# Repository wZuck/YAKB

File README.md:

# YAKB — Yet Another KeyBoard

[简体中文](README.zh-CN.md) · [B1.1 soldering workbench](hardware/soldering/b1/index.html) · [Assembly notes](docs/modular/README.md) · [File/revision map](docs/file-map.md)

The current assembly is the **B1.1 engineering prototype**: NiZ electrocapacitive mechanisms, a fixed 60-key HHKB layout, centered-stem 6u spacebar, nice!nano v2 / nRF52840 and ZMK, USB / BLE and a protected 1S battery.

The controller sits on a rear-left carrier, with USB-C directly accessible from the left side. Mainboard U1 takes only a passive interposer: **do not install a second controller there**. PCB, plate, case, fabrication files and geometry-based renders are supplied. Physical assembly, noise, RF, temperature and runtime remain untested. Qualify NiZ/stabilizer coupons, the short FPC and the rear-pod coupon before a complete build.

| Item | Current B1.1 definition |
| --- | --- |
| Layout | 60 keys, HHKB Control position, split right Shift + Fn; left blocker 1.5u, right 2.5u; centered 6u space with 95.25 mm stabilizer spacing |
| Mechanism / plate | NiZ housing, MX-cross slider, silencing ring, separate dome and sensing conical spring; 1.6 mm plate with initial 14.0 mm R0.5 cutouts; qualify in final material |
| Sensing mainboard | Shared A0 four-layer board, 285 × 94.6 × 1.6 mm; no MCU at U1 |
| Daughterboards / FPC | 82 × 24 × 1 mm carrier, 40 × 19 × 1 mm interposer; 24-conductor custom shaped FPC and Molex 200528-0240 connectors |
| Hand assembly | Mainly SOIC, 0805 and through holes; the 1 mm-pitch FPC connectors need flux and magnification; no bare MCU, crystal or RF network assembly |
| Power | Protected 1S, approximately 100 mA default charging, BOOST open; multiple pouches require a factory 1S2P / 1S3P pack with one protection board |
| USB / BLE | Direct to the carrier's nice!nano; Fn+5 selects USB, Fn+6 selects BLE; one reporting endpoint at a time |
| Case | Dedicated B1 base and pod lid with shared A0 HHKB bezel and plate; maximum plan envelope 299 × 136.6 mm, with 28 mm extra depth only at the rear-left pod; no visible top screws |
| Case compatibility | Mainboard mounts reference GH60 / Lot60; the B1 pod is not a universal drop-in fit for commercial GH60 / Poker cases |

B1.1 has **46 populated board/harness positions + one FPC**, plus one mainboard-U1 DNP record and 60 unsoldered sensing cells. No per-key diodes, hot-swap sockets, RGB, display or separate USB controller are used.

File entry points:

- [Complete electronics BOM](hardware/modular/BOM-B1-complete.csv), [module/case delta BOM](hardware/modular/BOM-B1.csv), [FPC pin map](hardware/modular/FPC-pinout.csv). The electronics BOM excludes batteries, mechanisms and case hardware; use the assembly notes and delta BOM for those.
- [Mainboard PCB](hardware/YAKB.kicad_pcb), [mainboard schematic](hardware/YAKB.kicad_sch), [controller PCB](hardware/modular/YAKB-controller-B1.kicad_pcb), [interposer PCB](hardware/modular/YAKB-interposer-B1.kicad_pcb), [custom FPC](hardware/modular/YAKB-shaped-FPC-B1.kicad_pcb). The shared mainboard source retains the A0 controller symbol; the consolidated BOM controls B1 population.
- [B1 assembly STEP](mechanical/modular/assembly_B1.step), [single-bay base STL](mechanical/modular/case_base_B1.stl), [three-bay base STL](mechanical/modular/case_base_B1_three_bay.stl), [pod lid](mechanical/modular/pod_lid_B1.stl), [shared bezel](mechanical/case_bezel.stl).
- [Own-case plate DXF](mechanical/plate_case.dxf), [NiZ coupon](mechanical/niz_fit_coupon.stl), [short-FPC ZIP](fabrication/modular/YAKB-FPC-coupon-B1.zip), [rear-pod print coupon](mechanical/modular/rear_pod_fit_coupon.stl). DXF units are mm; do not cut `REFERENCE`.
- [Interface corrections and qualification](docs/modular/interface-review.md), [firmware/flashing](firmware/README.md), [reproduction](docs/reproduce.md), [sources/licenses](docs/sources.md).

Scripts check native electrical reports, selected solid clearances, fabrication ZIPs and render hashes. See [reports](reports/) and the [consistency audit](docs/consistency-review.md) for coverage and pending physical tests. File checks do not certify hardware operation.

A0 is the baseline for the shared mainboard, bezel and plate. Its [historical workbench](hardware/soldering/index.html), [case record](docs/case-design.md), [base electrical analysis](docs/electrical-analysis.md) and [battery study](docs/battery-options.md) are explicitly scoped. The A0 base and incomplete USB extension arrangement are not used by the current B1 assembly.

Original YAKB files use MIT; reused Tako / KiCad library material retains its own licenses. See the source record for attribution boundaries.

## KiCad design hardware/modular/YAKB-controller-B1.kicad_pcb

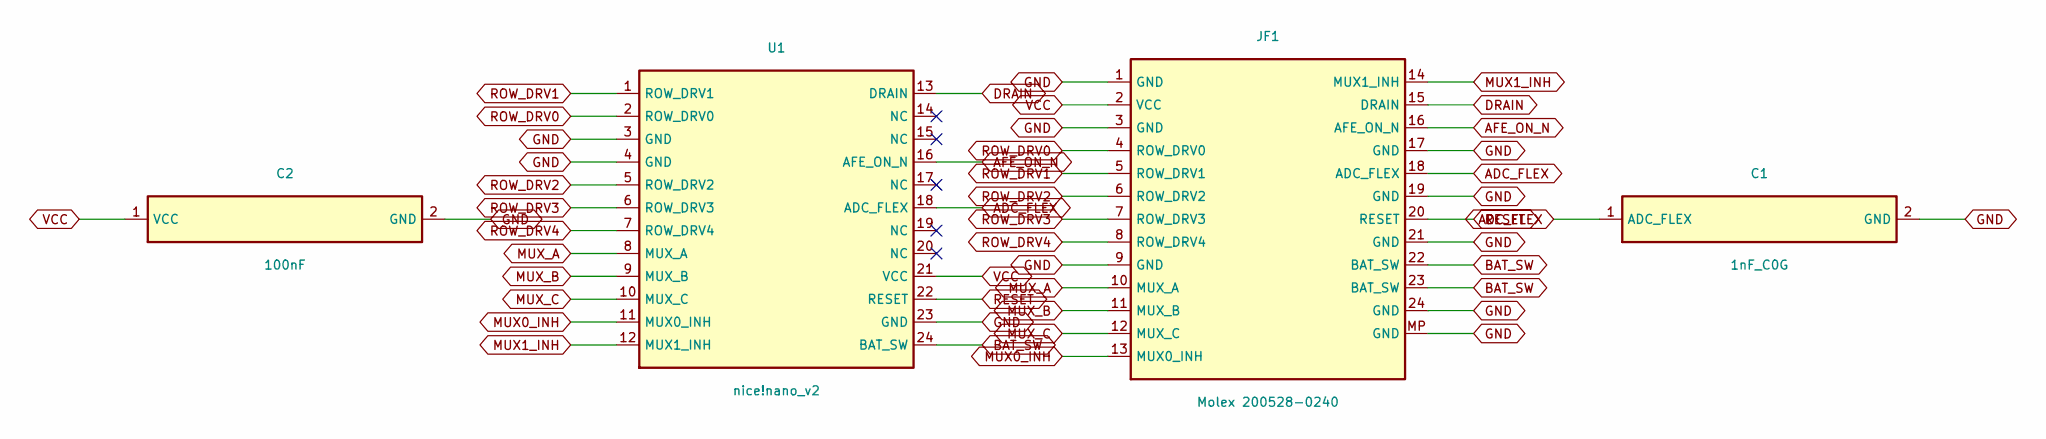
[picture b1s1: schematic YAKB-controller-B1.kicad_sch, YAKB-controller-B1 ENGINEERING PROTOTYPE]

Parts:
C1: 1nF_C0G; C_0805_2012Metric_Pad1.18x1.45mm_HandSolder
C2: 100nF; C_0805_2012Metric_Pad1.18x1.45mm_HandSolder
JF1: Molex 200528-0240; Molex_200528-0240_1x24-1MP_P1.00mm_Horizontal
U1: nice!nano_v2; nice_nano

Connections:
ADC_FLEX: C1.1 (ADC_FLEX), JF1.18 (ADC_FLEX), U1.18 (ADC_FLEX)
AFE_ON_N: JF1.16 (AFE_ON_N), U1.16 (AFE_ON_N)
BAT_SW: JF1.22 (BAT_SW), JF1.23 (BAT_SW), U1.24 (BAT_SW)
DRAIN: JF1.15 (DRAIN), U1.13 (DRAIN)
GND: C1.2 (GND), C2.2 (GND), JF1.1 (GND), JF1.3 (GND), JF1.9 (GND), JF1.17 (GND), JF1.19 (GND), JF1.21 (GND), JF1.24 (GND), JF1.MP (GND), U1.3 (GND), U1.4 (GND), U1.23 (GND)
MUX0_INH: JF1.13 (MUX0_INH), U1.11 (MUX0_INH)
MUX1_INH: JF1.14 (MUX1_INH), U1.12 (MUX1_INH)
MUX_A: JF1.10 (MUX_A), U1.8 (MUX_A)
MUX_B: JF1.11 (MUX_B), U1.9 (MUX_B)
MUX_C: JF1.12 (MUX_C), U1.10 (MUX_C)
RESET: JF1.20 (RESET), U1.22 (RESET)
ROW_DRV0: JF1.4 (ROW_DRV0), U1.2 (ROW_DRV0)
ROW_DRV1: JF1.5 (ROW_DRV1), U1.1 (ROW_DRV1)
ROW_DRV2: JF1.6 (ROW_DRV2), U1.5 (ROW_DRV2)
ROW_DRV3: JF1.7 (ROW_DRV3), U1.6 (ROW_DRV3)
ROW_DRV4: JF1.8 (ROW_DRV4), U1.7 (ROW_DRV4)
VCC: C2.1 (VCC), JF1.2 (VCC), U1.21 (VCC)

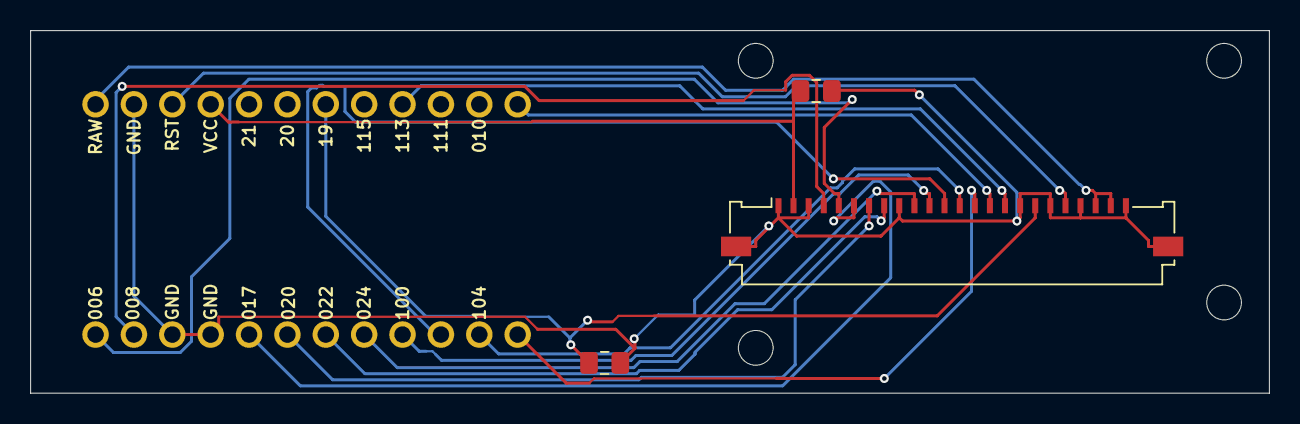
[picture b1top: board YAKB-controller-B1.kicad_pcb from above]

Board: 2 copper layers, 82.0 x 24.0 mm, 8 parts (0 on the bottom side), 17 nets.

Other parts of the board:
H1, H2, H3, H4: (no value)

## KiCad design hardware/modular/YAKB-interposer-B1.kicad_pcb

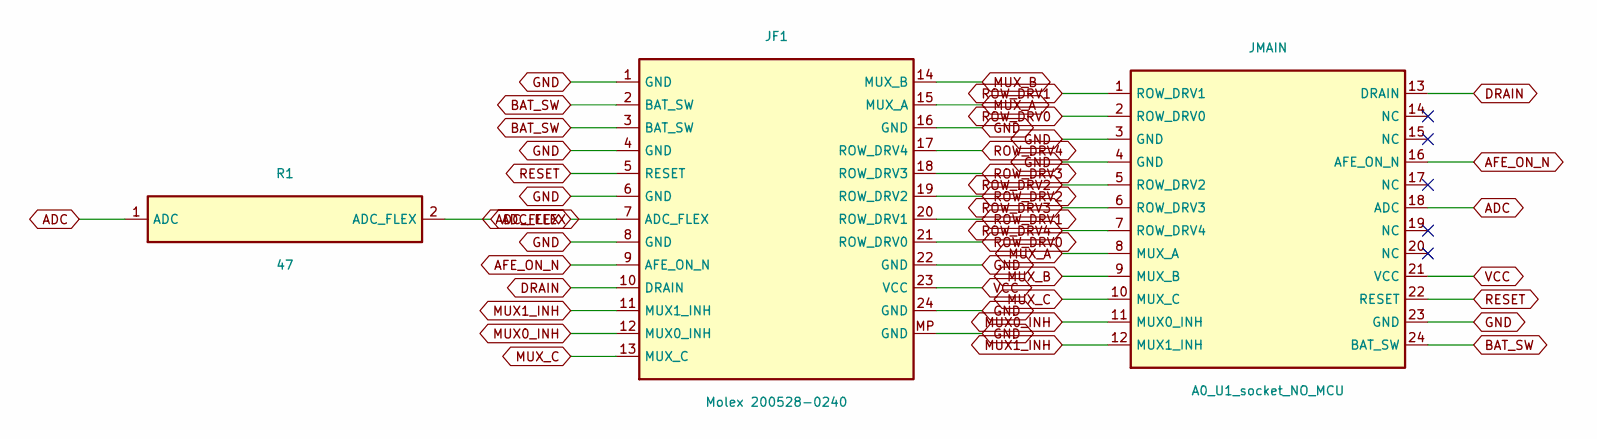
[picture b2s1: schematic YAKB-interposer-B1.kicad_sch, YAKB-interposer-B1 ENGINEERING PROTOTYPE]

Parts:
JF1: Molex 200528-0240; Molex_200528-0240_1x24-1MP_P1.00mm_Horizontal
JMAIN: A0_U1_socket_NO_MCU; A0_U1_socket_adapter
R1: 47; R_0805_2012Metric_Pad1.20x1.40mm_HandSolder

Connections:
ADC: JMAIN.18 (ADC), R1.1 (ADC)
ADC_FLEX: JF1.7 (ADC_FLEX), R1.2 (ADC_FLEX)
AFE_ON_N: JF1.9 (AFE_ON_N), JMAIN.16 (AFE_ON_N)
BAT_SW: JF1.2 (BAT_SW), JF1.3 (BAT_SW), JMAIN.24 (BAT_SW)
DRAIN: JF1.10 (DRAIN), JMAIN.13 (DRAIN)
GND: JF1.1 (GND), JF1.4 (GND), JF1.6 (GND), JF1.8 (GND), JF1.16 (GND), JF1.22 (GND), JF1.24 (GND), JF1.MP (GND), JMAIN.3 (GND), JMAIN.4 (GND), JMAIN.23 (GND)
MUX0_INH: JF1.12 (MUX0_INH), JMAIN.11 (MUX0_INH)
MUX1_INH: JF1.11 (MUX1_INH), JMAIN.12 (MUX1_INH)
MUX_A: JF1.15 (MUX_A), JMAIN.8 (MUX_A)
MUX_B: JF1.14 (MUX_B), JMAIN.9 (MUX_B)
MUX_C: JF1.13 (MUX_C), JMAIN.10 (MUX_C)
RESET: JF1.5 (RESET), JMAIN.22 (RESET)
ROW_DRV0: JF1.21 (ROW_DRV0), JMAIN.2 (ROW_DRV0)
ROW_DRV1: JF1.20 (ROW_DRV1), JMAIN.1 (ROW_DRV1)
ROW_DRV2: JF1.19 (ROW_DRV2), JMAIN.5 (ROW_DRV2)
ROW_DRV3: JF1.18 (ROW_DRV3), JMAIN.6 (ROW_DRV3)
ROW_DRV4: JF1.17 (ROW_DRV4), JMAIN.7 (ROW_DRV4)
VCC: JF1.23 (VCC), JMAIN.21 (VCC)

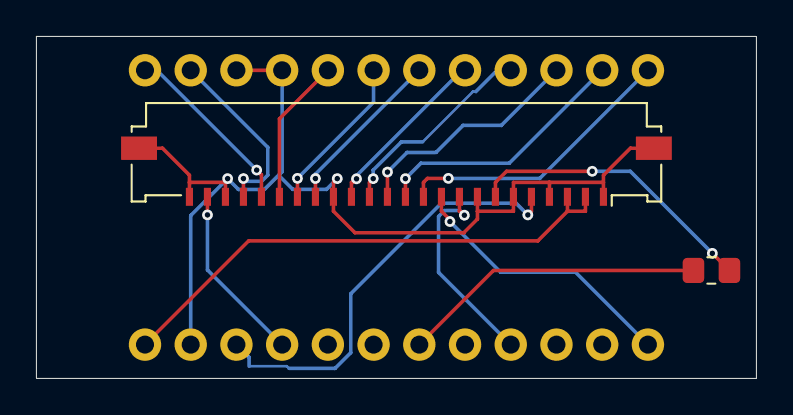
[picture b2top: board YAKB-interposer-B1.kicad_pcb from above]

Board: 2 copper layers, 40.0 x 19.0 mm, 3 parts (0 on the bottom side), 18 nets.

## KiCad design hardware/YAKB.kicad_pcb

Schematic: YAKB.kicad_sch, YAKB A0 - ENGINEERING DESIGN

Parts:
C1, C2, C3: 100n; C_0805_2012Metric_Pad1.18x1.45mm_HandSolder
C4: 220p_C0G; C_0805_2012Metric_Pad1.18x1.45mm_HandSolder
C5: 1u; C_0805_2012Metric_Pad1.18x1.45mm_HandSolder
EC1: Esc; ecs_pad_1U_no_ring
EC2: 1; ecs_pad_1U_no_ring
EC3: 2; ecs_pad_1U_no_ring
EC4: 3; ecs_pad_1U_no_ring
EC5: 4; ecs_pad_1U_no_ring
EC6: 5; ecs_pad_1U_no_ring
EC7: 6; ecs_pad_1U_no_ring
EC8: 7; ecs_pad_1U_no_ring
EC9: 8; ecs_pad_1U_no_ring
EC10: 9; ecs_pad_1U_no_ring
EC11: 0; ecs_pad_1U_no_ring
EC12: -; ecs_pad_1U_no_ring
EC13: =; ecs_pad_1U_no_ring
EC14: \; ecs_pad_1U_no_ring
EC15: `; ecs_pad_1U_no_ring
EC16: Tab; ecs_pad_1U_no_ring
EC17: Q; ecs_pad_1U_no_ring
EC18: W; ecs_pad_1U_no_ring
EC19: E; ecs_pad_1U_no_ring
EC20: R; ecs_pad_1U_no_ring
EC21: T; ecs_pad_1U_no_ring
EC22: Y; ecs_pad_1U_no_ring
EC23: U; ecs_pad_1U_no_ring
EC24: I; ecs_pad_1U_no_ring
EC25: O; ecs_pad_1U_no_ring
EC26: P; ecs_pad_1U_no_ring
EC27: [; ecs_pad_1U_no_ring
EC28: ]; ecs_pad_1U_no_ring
EC29: Backspace; ecs_pad_1U_no_ring
EC30: Control; ecs_pad_1U_no_ring
EC31: A; ecs_pad_1U_no_ring
EC32: S; ecs_pad_1U_no_ring
EC33: D; ecs_pad_1U_no_ring
EC34: F; ecs_pad_1U_no_ring
EC35: G; ecs_pad_1U_no_ring
EC36: H; ecs_pad_1U_no_ring
EC37: J; ecs_pad_1U_no_ring
EC38: K; ecs_pad_1U_no_ring
EC39: L; ecs_pad_1U_no_ring
EC40: ;; ecs_pad_1U_no_ring
EC41: '; ecs_pad_1U_no_ring
EC42: Enter; ecs_pad_1U_no_ring
EC43: Shift; ecs_pad_1U_no_ring
EC44: Z; ecs_pad_1U_no_ring
EC45: X; ecs_pad_1U_no_ring
EC46: C; ecs_pad_1U_no_ring
EC47: V; ecs_pad_1U_no_ring
EC48: B; ecs_pad_1U_no_ring
EC49: N; ecs_pad_1U_no_ring
EC50: M; ecs_pad_1U_no_ring
EC51: ,; ecs_pad_1U_no_ring
EC52: .; ecs_pad_1U_no_ring
EC53: /; ecs_pad_1U_no_ring
EC54: RShift; ecs_pad_1U_no_ring
EC55: Fn; ecs_pad_1U_no_ring
EC56: LGUI; ecs_pad_1U_no_ring
EC57: LAlt; ecs_pad_1U_no_ring
EC58: Space; ecs_pad_1U_no_ring
EC59: RAlt; ecs_pad_1U_no_ring
EC60: RGUI; ecs_pad_1U_no_ring
J1: JST_S2B-PH-K; Battery_PH2
Q1: AO3401A; SOT-23
R1, R2, R3, R4, R5: 100; R_0805_2012Metric_Pad1.20x1.40mm_HandSolder
R10, R11, R12, R13, R14, R15, R16, R17, R18, R19, R20, R21, R22, R23, R24, R30, R33, R34, R35: 100k; R_0805_2012Metric_Pad1.20x1.40mm_HandSolder
R31, R32, R36: 1k; R_0805_2012Metric_Pad1.20x1.40mm_HandSolder
SW1: Battery_switch_pigtail; SPST_PIGTAIL_2.54
SW2: Reset_NO; RESET_2.54_TH
U1: nice!nano_v2; nice_nano
U2, U3: CD74HC4051M96; SOIC-16_3.9x9.9mm_P1.27mm
U4: OPA350UA; SOIC-8_3.9x4.9mm_P1.27mm

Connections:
ADC: R30.1 (ADC), U1.18 (D19/P0.02/AIN0), U4.6 (OUT)
AFE_3V3: C3.1 (AFE_3V3), Q1.3 (D), U4.7 (V+)
AFE_GATE: Q1.1 (G), R35.1 (AFE_GATE), R36.2 (AFE_GATE)
AFE_ON_N: R36.1 (AFE_ON_N), U1.16 (D15/P1.13)
BAT_RAW: J1.1 (BAT_RAW), SW1.1 (BAT_RAW)
BAT_SW: SW1.2 (BAT_SW), U1.24 (BATTERY+)
COL0: EC1.2 (SENSE), EC16.2 (SENSE), EC30.2 (SENSE), R10.1 (COL0), U2.13 (X0)
COL1: EC2.2 (SENSE), EC43.2 (SENSE), R11.1 (COL1), U2.14 (X1)
COL2: EC3.2 (SENSE), EC17.2 (SENSE), EC31.2 (SENSE), EC44.2 (SENSE), EC56.2 (SENSE), R12.1 (COL2), U2.15 (X2)
COL3: EC4.2 (SENSE), EC18.2 (SENSE), EC32.2 (SENSE), EC45.2 (SENSE), EC57.2 (SENSE), R13.1 (COL3), U2.12 (X3)
COL4: EC5.2 (SENSE), EC19.2 (SENSE), EC33.2 (SENSE), EC46.2 (SENSE), R14.1 (COL4), U2.1 (X4)
COL5: EC6.2 (SENSE), EC20.2 (SENSE), EC34.2 (SENSE), EC47.2 (SENSE), R15.1 (COL5), U2.5 (X5)
COL6: EC7.2 (SENSE), EC21.2 (SENSE), EC35.2 (SENSE), EC48.2 (SENSE), R16.1 (COL6), U2.2 (X6)
COL7: EC8.2 (SENSE), EC22.2 (SENSE), EC36.2 (SENSE), EC49.2 (SENSE), EC58.2 (SENSE), R17.1 (COL7), U2.4 (X7)
COL8: EC9.2 (SENSE), EC23.2 (SENSE), EC37.2 (SENSE), EC50.2 (SENSE), R18.1 (COL8), U3.13 (X0)
COL9: EC10.2 (SENSE), EC24.2 (SENSE), EC38.2 (SENSE), EC51.2 (SENSE), R19.1 (COL9), U3.14 (X1)
COL10: EC11.2 (SENSE), EC25.2 (SENSE), EC39.2 (SENSE), EC52.2 (SENSE), EC59.2 (SENSE), R20.1 (COL10), U3.15 (X2)
COL11: EC12.2 (SENSE), EC26.2 (SENSE), EC40.2 (SENSE), EC53.2 (SENSE), R21.1 (COL11), U3.12 (X3)
COL12: EC13.2 (SENSE), EC27.2 (SENSE), EC41.2 (SENSE), EC60.2 (SENSE), R22.1 (COL12), U3.1 (X4)
COL13: EC14.2 (SENSE), EC28.2 (SENSE), EC42.2 (SENSE), EC54.2 (SENSE), R23.1 (COL13), U3.5 (X5)
COL14: EC15.2 (SENSE), EC29.2 (SENSE), EC55.2 (SENSE), R24.1 (COL14), U3.2 (X6)
DRAIN: R32.1 (DRAIN), U1.13 (D10/P0.09)
FB: R30.2 (FB), R31.1 (FB), U4.2 (IN-)
GND: C1.2 (GND), C2.2 (GND), C3.2 (GND), C4.2 (GND), C5.2 (GND), EC1.3 (GUARD), EC2.3 (GUARD), EC3.3 (GUARD), EC4.3 (GUARD), EC5.3 (GUARD), EC6.3 (GUARD), EC7.3 (GUARD), EC8.3 (GUARD), EC9.3 (GUARD), EC10.3 (GUARD), EC11.3 (GUARD), EC12.3 (GUARD), EC13.3 (GUARD), EC14.3 (GUARD), EC15.3 (GUARD), EC16.3 (GUARD), EC17.3 (GUARD), EC18.3 (GUARD), EC19.3 (GUARD), EC20.3 (GUARD), EC21.3 (GUARD), EC22.3 (GUARD), EC23.3 (GUARD), EC24.3 (GUARD), EC25.3 (GUARD), EC26.3 (GUARD), EC27.3 (GUARD), EC28.3 (GUARD), EC29.3 (GUARD), EC30.3 (GUARD), EC31.3 (GUARD), EC32.3 (GUARD), EC33.3 (GUARD), EC34.3 (GUARD), EC35.3 (GUARD), EC36.3 (GUARD), EC37.3 (GUARD), EC38.3 (GUARD), EC39.3 (GUARD), EC40.3 (GUARD), EC41.3 (GUARD), EC42.3 (GUARD), EC43.3 (GUARD), EC44.3 (GUARD), EC45.3 (GUARD), EC46.3 (GUARD), EC47.3 (GUARD), EC48.3 (GUARD), EC49.3 (GUARD), EC50.3 (GUARD), EC51.3 (GUARD), EC52.3 (GUARD), EC53.3 (GUARD), EC54.3 (GUARD), EC55.3 (GUARD), EC56.3 (GUARD), EC57.3 (GUARD), EC58.3 (GUARD), EC59.3 (GUARD), EC60.3 (GUARD), J1.2 (GND), R10.2 (GND), R11.2 (GND), R12.2 (GND), R13.2 (GND), R14.2 (GND), R15.2 (GND), R16.2 (GND), R17.2 (GND), R18.2 (GND), R19.2 (GND), R20.2 (GND), R21.2 (GND), R22.2 (GND), R23.2 (GND), R24.2 (GND), R31.2 (GND), SW2.2 (GND), U1.3 (GND), U1.4 (GND), U1.23 (GND), U2.7 (VEE), U2.8 (GND), U3.4 (X7), U3.7 (VEE), U3.8 (GND), U4.4 (V-)
MUX0_INH: R33.1 (MUX0_INH), U1.11 (D8/P1.04), U2.6 (INH)
MUX1_INH: R34.1 (MUX1_INH), U1.12 (D9/P1.06), U3.6 (INH)
MUX_A: U1.8 (D5/P0.24), U2.11 (A), U3.11 (A)
MUX_B: U1.9 (D6/P1.00), U2.10 (B), U3.10 (B)
MUX_C: U1.10 (D7/P0.11), U2.9 (C), U3.9 (C)
RESET: SW2.1 (RESET), U1.22 (RESET)
ROW0: EC1.1 (DRIVE), EC2.1 (DRIVE), EC3.1 (DRIVE), EC4.1 (DRIVE), EC5.1 (DRIVE), EC6.1 (DRIVE), EC7.1 (DRIVE), EC8.1 (DRIVE), EC9.1 (DRIVE), EC10.1 (DRIVE), EC11.1 (DRIVE), EC12.1 (DRIVE), EC13.1 (DRIVE), EC14.1 (DRIVE), EC15.1 (DRIVE), R1.2 (ROW0)
ROW1: EC16.1 (DRIVE), EC17.1 (DRIVE), EC18.1 (DRIVE), EC19.1 (DRIVE), EC20.1 (DRIVE), EC21.1 (DRIVE), EC22.1 (DRIVE), EC23.1 (DRIVE), EC24.1 (DRIVE), EC25.1 (DRIVE), EC26.1 (DRIVE), EC27.1 (DRIVE), EC28.1 (DRIVE), EC29.1 (DRIVE), R2.2 (ROW1)
ROW2: EC30.1 (DRIVE), EC31.1 (DRIVE), EC32.1 (DRIVE), EC33.1 (DRIVE), EC34.1 (DRIVE), EC35.1 (DRIVE), EC36.1 (DRIVE), EC37.1 (DRIVE), EC38.1 (DRIVE), EC39.1 (DRIVE), EC40.1 (DRIVE), EC41.1 (DRIVE), EC42.1 (DRIVE), R3.2 (ROW2)
ROW3: EC43.1 (DRIVE), EC44.1 (DRIVE), EC45.1 (DRIVE), EC46.1 (DRIVE), EC47.1 (DRIVE), EC48.1 (DRIVE), EC49.1 (DRIVE), EC50.1 (DRIVE), EC51.1 (DRIVE), EC52.1 (DRIVE), EC53.1 (DRIVE), EC54.1 (DRIVE), EC55.1 (DRIVE), R4.2 (ROW3)
ROW4: EC56.1 (DRIVE), EC57.1 (DRIVE), EC58.1 (DRIVE), EC59.1 (DRIVE), EC60.1 (DRIVE), R5.2 (ROW4)
ROW_DRV0: R1.1 (ROW_DRV0), U1.2 (D0/P0.08)
ROW_DRV1: R2.1 (ROW_DRV1), U1.1 (D1/P0.06)
ROW_DRV2: R3.1 (ROW_DRV2), U1.5 (D2/P0.17)
ROW_DRV3: R4.1 (ROW_DRV3), U1.6 (D3/P0.20)
ROW_DRV4: R5.1 (ROW_DRV4), U1.7 (D4/P0.22)
SENSE: C4.1 (SENSE), R32.2 (SENSE), U2.3 (COM), U3.3 (COM), U4.3 (IN+)
VCC: C1.1 (VCC), C2.1 (VCC), C5.1 (VCC), Q1.2 (S), R33.2 (VCC), R34.2 (VCC), R35.2 (VCC), U1.21 (VCC_3.3V), U2.16 (VCC), U3.16 (VCC)

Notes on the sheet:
YAKB A0 | NiZ EC + HHKB 6u + nice!nano v2 | ENGINEERING PROTOTYPE
Physical pin numbers and named nets are authoritative. USB is an external passive data extension to U1.
U2/U3: only one INH low at a time. U4 gain 101. DRAIN goes through R32 to SENSE. Q1 gates U4 only.
SW1/SW2 are 2.54mm solder-hole harnesses. No external 5V connection to U1 BATTERY+.
EC electrodes: logical row = physical row; column = floor(x_u + width_u/2), including empty column bins.

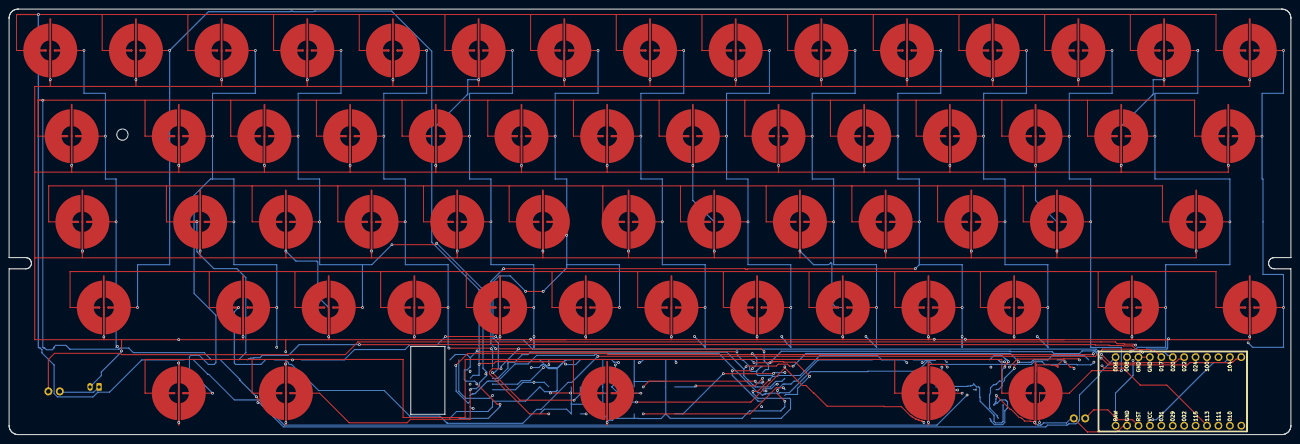
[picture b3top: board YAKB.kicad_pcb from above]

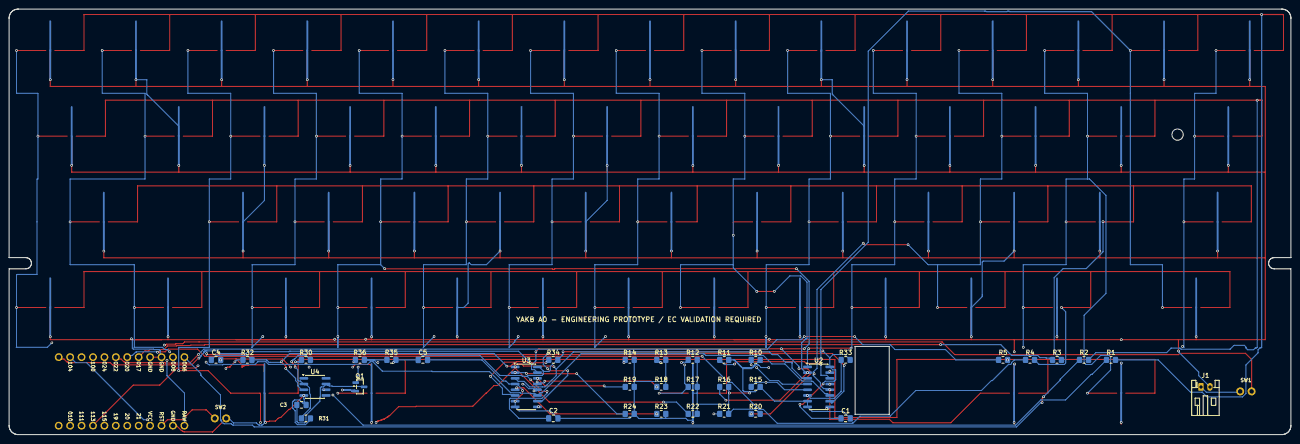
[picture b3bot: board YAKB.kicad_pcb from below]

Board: 4 copper layers, 285.0 x 94.6 mm, 103 parts (40 on the bottom side), 42 nets.

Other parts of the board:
H_center: (no value)
H_lower_center: (no value)
H_upper_left: (no value)

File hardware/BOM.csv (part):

Reference,Value,Footprint,Side,X_mm,Y_mm,Status
U1,nice!nano_v2,YAKB:nice_nano,B,260.0,85.0,selection; verify procurement
U2,SN74HC4051D,Package_SO:SOIC-16_3.9x9.9mm_P1.27mm,B,105,84,selection; verify procurement
U3,SN74HC4051D,Package_SO:SOIC-16_3.9x9.9mm_P1.27mm,B,170,84,selection; verify procurement
U4,OPA350UA,Package_SO:SOIC-8_3.9x4.9mm_P1.27mm,B,217,84,selection; verify procurement
Q1,AO3401A,Package_TO_SOT_SMD:SOT-23,B,207,84,selection; verify procurement
R1,100,Resistor_SMD:R_0805_2012Metric_Pad1.20x1.40mm_HandSolder,B,40,78,selection; verify procurement
R2,100,Resistor_SMD:R_0805_2012Metric_Pad1.20x1.40mm_HandSolder,B,46,78,selection; verify procurement
R3,100,Resistor_SMD:R_0805_2012Metric_Pad1.20x1.40mm_HandSolder,B,52,78,selection; verify procurement
R4,100,Resistor_SMD:R_0805_2012Metric_Pad1.20x1.40mm_HandSolder,B,58,78,selection; verify procurement
R5,100,Resistor_SMD:R_0805_2012Metric_Pad1.20x1.40mm_HandSolder,B,64,78,selection; verify procurement
R10,100k,Resistor_SMD:R_0805_2012Metric_Pad1.20x1.40mm_HandSolder,B,119,78,selection; verify procurement
R11,100k,Resistor_SMD:R_0805_2012Metric_Pad1.20x1.40mm_HandSolder,B,126,78,selection; verify procurement
R12,100k,Resistor_SMD:R_0805_2012Metric_Pad1.20x1.40mm_HandSolder,B,133,78,selection; verify procurement
R13,100k,Resistor_SMD:R_0805_2012Metric_Pad1.20x1.40mm_HandSolder,B,140,78,selection; verify procurement
R14,100k,Resistor_SMD:R_0805_2012Metric_Pad1.20x1.40mm_HandSolder,B,147,78,selection; verify procurement
R15,100k,Resistor_SMD:R_0805_2012Metric_Pad1.20x1.40mm_HandSolder,B,119,84,selection; verify procurement
R16,100k,Resistor_SMD:R_0805_2012Metric_Pad1.20x1.40mm_HandSolder,B,126,84,selection; verify procurement
R17,100k,Resistor_SMD:R_0805_2012Metric_Pad1.20x1.40mm_HandSolder,B,133,84,selection; verify procurement
R18,100k,Resistor_SMD:R_0805_2012Metric_Pad1.20x1.40mm_HandSolder,B,140,84,selection; verify procurement
R19,100k,Resistor_SMD:R_0805_2012Metric_Pad1.20x1.40mm_HandSolder,B,147,84,selection; verify procurement
R20,100k,Resistor_SMD:R_0805_2012Metric_Pad1.20x1.40mm_HandSolder,B,119,90,selection; verify procurement
R21,100k,Resistor_SMD:R_0805_2012Metric_Pad1.20x1.40mm_HandSolder,B,126,90,selection; verify procurement
R22,100k,Resistor_SMD:R_0805_2012Metric_Pad1.20x1.40mm_HandSolder,B,133,90,selection; verify procurement
R23,100k,Resistor_SMD:R_0805_2012Metric_Pad1.20x1.40mm_HandSolder,B,140,90,selection; verify procurement
R24,100k,Resistor_SMD:R_0805_2012Metric_Pad1.20x1.40mm_HandSolder,B,147,90,selection; verify procurement
R30,100k,Resistor_SMD:R_0805_2012Metric_Pad1.20x1.40mm_HandSolder,B,219,78,selection; verify procurement
R31,1k,Resistor_SMD:R_0805_2012Metric_Pad1.20x1.40mm_HandSolder,B,219,91,selection; verify procurement
R32,1k,Resistor_SMD:R_0805_2012Metric_Pad1.20x1.40mm_HandSolder,B,232,78,selection; verify procurement
R33,100k,Resistor_SMD:R_0805_2012Metric_Pad1.20x1.40mm_HandSolder,B,99,78,selection; verify procurement
R34,100k,Resistor_SMD:R_0805_2012Metric_Pad1.20x1.40mm_HandSolder,B,164,78,selection; verify procurement
R35,100k,Resistor_SMD:R_0805_2012Metric_Pad1.20x1.40mm_HandSolder,B,200,78,selection; verify procurement
R36,1k,Resistor_SMD:R_0805_2012Metric_Pad1.20x1.40mm_HandSolder,B,207,78,selection; verify procurement
C1,100n,Capacitor_SMD:C_0805_2012Metric_Pad1.18x1.45mm_HandSolder,B,99,91,selection; verify procurement
C2,100n,Capacitor_SMD:C_0805_2012Metric_Pad1.18x1.45mm_HandSolder,B,164,91,selection; verify procurement
C3,100n,Capacitor_SMD:C_0805_2012Metric_Pad1.18x1.45mm_HandSolder,B,220,88,selection; verify procurement
C4,220p_C0G,Capacitor_SMD:C_0805_2012Metric_Pad1.18x1.45mm_HandSolder,B,239,78,selection; verify procurement
C5,1u,Capacitor_SMD:C_0805_2012Metric_Pad1.18x1.45mm_HandSolder,B,193,78,selection; verify procurement
J1,JST_S2B-PH-K,YAKB:Battery_PH2,B,20,84,selection; verify procurement
SW1,Battery_switch_pigtail,YAKB:SPST_PIGTAIL_2.54,B,10,85,selection; verify procurement
SW2,Reset_NO,YAKB:RESET_2.54_TH,B,238,91,selection; verify procurement
EC1,Esc,YAKB:ecs_pad_1U_no_ring,F,9.15,9.2,EC electrode
EC2,1,YAKB:ecs_pad_1U_no_ring,F,28.200000000000003,9.2,EC electrode
EC3,2,YAKB:ecs_pad_1U_no_ring,F,47.25,9.2,EC electrode
EC4,3,YAKB:ecs_pad_1U_no_ring,F,66.30000000000001,9.2,EC electrode
EC5,4,YAKB:ecs_pad_1U_no_ring,F,85.35000000000001,9.2,EC electrode
EC6,5,YAKB:ecs_pad_1U_no_ring,F,104.4,9.2,EC electrode
EC7,6,YAKB:ecs_pad_1U_no_ring,F,123.45000000000002,9.2,EC electrode
EC8,7,YAKB:ecs_pad_1U_no_ring,F,142.5,9.2,EC electrode
EC9,8,YAKB:ecs_pad_1U_no_ring,F,161.55,9.2,EC electrode
EC10,9,YAKB:ecs_pad_1U_no_ring,F,180.60000000000002,9.2,EC electrode
EC11,0,YAKB:ecs_pad_1U_no_ring,F,199.65,9.2,EC electrode
EC12,-,YAKB:ecs_pad_1U_no_ring,F,218.70000000000002,9.2,EC electrode
EC13,=,YAKB:ecs_pad_1U_no_ring,F,237.75000000000003,9.2,EC electrode
EC14,\,YAKB:ecs_pad_1U_no_ring,F,256.8,9.2,EC electrode
EC15,`,YAKB:ecs_pad_1U_no_ring,F,275.84999999999997,9.2,EC electrode
EC16,Tab,YAKB:ecs_pad_1U_no_ring,F,13.912500000000001,28.25,EC electrode
EC17,Q,YAKB:ecs_pad_1U_no_ring,F,37.725,28.25,EC electrode
EC18,W,YAKB:ecs_pad_1U_no_ring,F,56.775,28.25,EC electrode
EC19,E,YAKB:ecs_pad_1U_no_ring,F,75.825,28.25,EC electrode
EC20,R,YAKB:ecs_pad_1U_no_ring,F,94.87500000000001,28.25,EC electrode
EC21,T,YAKB:ecs_pad_1U_no_ring,F,113.92500000000001,28.25,EC electrode
EC22,Y,YAKB:ecs_pad_1U_no_ring,F,132.975,28.25,EC electrode
EC23,U,YAKB:ecs_pad_1U_no_ring,F,152.025,28.25,EC electrode
EC24,I,YAKB:ecs_pad_1U_no_ring,F,171.07500000000002,28.25,EC electrode
EC25,O,YAKB:ecs_pad_1U_no_ring,F,190.125,28.25,EC electrode
EC26,P,YAKB:ecs_pad_1U_no_ring,F,209.175,28.25,EC electrode
EC27,[,YAKB:ecs_pad_1U_no_ring,F,228.22500000000002,28.25,EC electrode
EC28,],YAKB:ecs_pad_1U_no_ring,F,247.275,28.25,EC electrode
EC29,Backspace,YAKB:ecs_pad_1U_no_ring,F,271.0875,28.25,EC electrode
EC30,Control,YAKB:ecs_pad_1U_no_ring,F,16.293750000000003,47.3,EC electrode
EC31,A,YAKB:ecs_pad_1U_no_ring,F,42.4875,47.3,EC electrode
EC32,S,YAKB:ecs_pad_1U_no_ring,F,61.5375,47.3,EC electrode
EC33,D,YAKB:ecs_pad_1U_no_ring,F,80.5875,47.3,EC electrode
EC34,F,YAKB:ecs_pad_1U_no_ring,F,99.6375,47.3,EC electrode
EC35,G,YAKB:ecs_pad_1U_no_ring,F,118.68750000000001,47.3,EC electrode
EC36,H,YAKB:ecs_pad_1U_no_ring,F,137.7375,47.3,EC electrode
EC37,J,YAKB:ecs_pad_1U_no_ring,F,156.78750000000002,47.3,EC electrode
EC38,K,YAKB:ecs_pad_1U_no_ring,F,175.8375,47.3,EC electrode
EC39,L,YAKB:ecs_pad_1U_no_ring,F,194.88750000000002,47.3,EC electrode
EC40,;,YAKB:ecs_pad_1U_no_ring,F,213.9375,47.3,EC electrode
EC41,',YAKB:ecs_pad_1U_no_ring,F,232.9875,47.3,EC electrode
EC42,Enter,YAKB:ecs_pad_1U_no_ring,F,263.94375,47.3,EC electrode
EC43,Shift,YAKB:ecs_pad_1U_no_ring,F,21.05625,66.35000000000001,EC electrode
EC44,Z,YAKB:ecs_pad_1U_no_ring,F,52.0125,66.35000000000001,EC electrode
EC45,X,YAKB:ecs_pad_1U_no_ring,F,71.0625,66.35000000000001,EC electrode
EC46,C,YAKB:ecs_pad_1U_no_ring,F,90.11250000000001,66.35000000000001,EC electrode
EC47,V,YAKB:ecs_pad_1U_no_ring,F,109.16250000000001,66.35000000000001,EC electrode
EC48,B,YAKB:ecs_pad_1U_no_ring,F,128.2125,66.35000000000001,EC electrode
EC49,N,YAKB:ecs_pad_1U_no_ring,F,147.26250000000002,66.35000000000001,EC electrode
EC50,M,YAKB:ecs_pad_1U_no_ring,F,166.3125,66.35000000000001,EC electrode
EC51,",",YAKB:ecs_pad_1U_no_ring,F,185.3625,66.35000000000001,EC electrode
EC52,.,YAKB:ecs_pad_1U_no_ring,F,204.41250000000002,66.35000000000001,EC electrode
EC53,/,YAKB:ecs_pad_1U_no_ring,F,223.4625,66.35000000000001,EC electrode
EC54,RShift,YAKB:ecs_pad_1U_no_ring,F,249.65625000000003,66.35000000000001,EC electrode
EC55,Fn,YAKB:ecs_pad_1U_no_ring,F,275.84999999999997,66.35000000000001,EC electrode
EC56,LGUI,YAKB:ecs_pad_1U_no_ring,F,37.725,85.4,EC electrode
EC57,LAlt,YAKB:ecs_pad_1U_no_ring,F,61.5375,85.4,EC electrode
EC58,Space,YAKB:ecs_pad_1U_no_ring,F,132.975,85.4,EC electrode
EC59,RAlt,YAKB:ecs_pad_1U_no_ring,F,204.41250000000002,85.4,EC electrode
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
